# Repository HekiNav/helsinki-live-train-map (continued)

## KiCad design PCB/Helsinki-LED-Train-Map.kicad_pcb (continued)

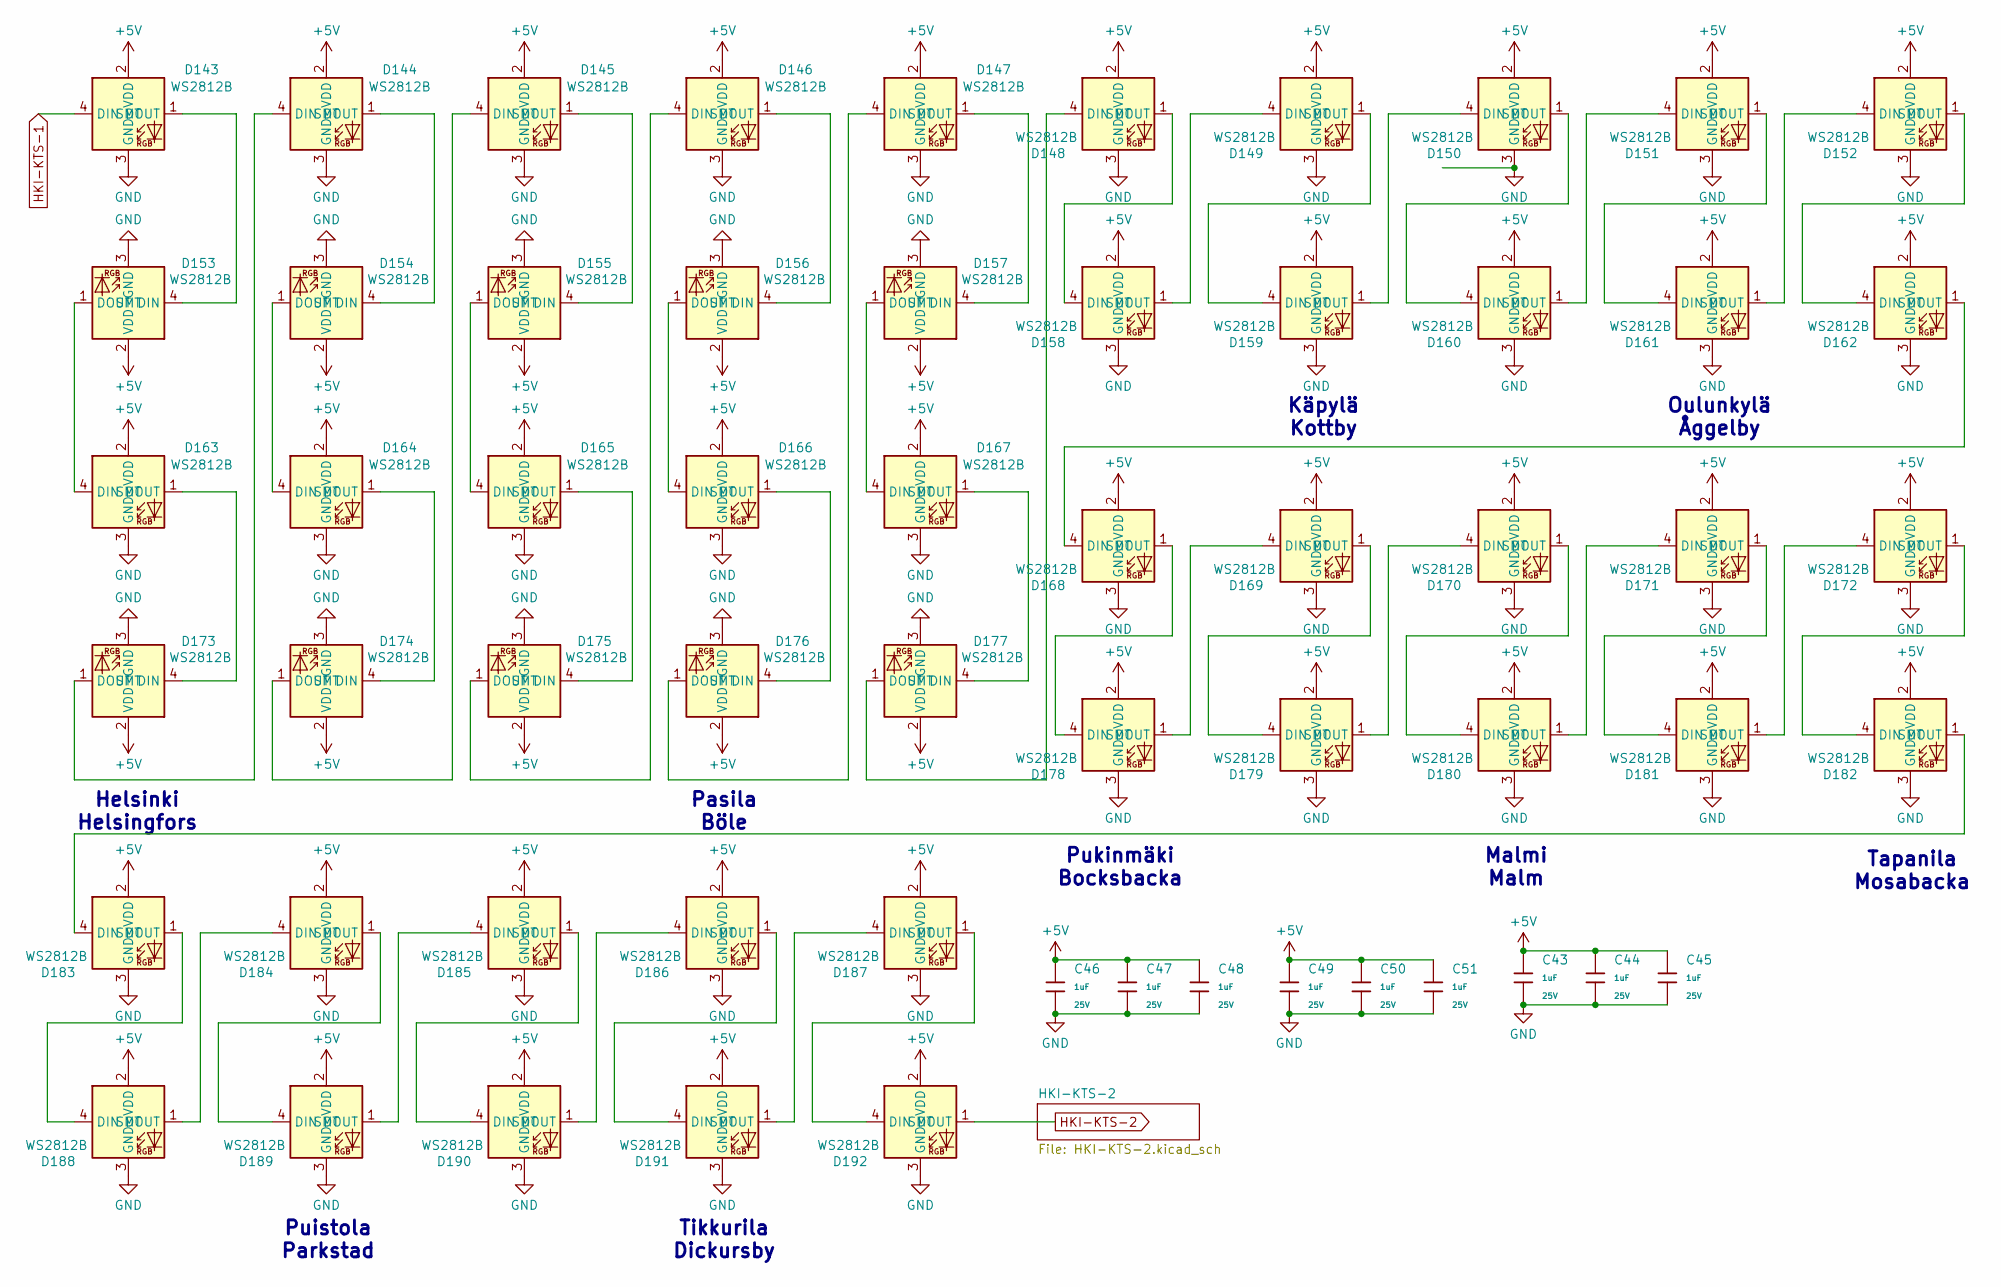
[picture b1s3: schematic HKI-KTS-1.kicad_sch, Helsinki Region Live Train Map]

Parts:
C43, C44, C45, C46, C47, C48, C49, C50, C51: 1uF; C_0402; Voltage Rated 25V; Tolerance ±10%; Part CL05A105KA5NQNC; LCSC C52923
D143, D144, D145, D146, D147, D148, D149, D150, D151, D152, D153, D154, D155, D156, D157, D158, D159, D160, D161, D162, D163, D164, D165, D166, D167, D168, D169, D170, D171, D172, D173, D174, D175, D176, D177, D178, D179, D180, D181, D182, D183, D184, D185, D186, D187, D188, D189, D190, D191, D192: WS2812B; LED-SMD_4P-L1.6-W1.5_XL-1615RGBC-WS2812B; Part XL-1615RGBC-WS2812B; LCSC C5349954

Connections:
+5V: C43.1, C44.1, C45.1, C46.1, C47.1, C48.1, C49.1, C50.1, C51.1, D143.2 (VDD), D144.2 (VDD), D145.2 (VDD), D146.2 (VDD), D147.2 (VDD), D148.2 (VDD), D149.2 (VDD), D150.2 (VDD), D151.2 (VDD), D152.2 (VDD), D153.2 (VDD), D154.2 (VDD), D155.2 (VDD), D156.2 (VDD), D157.2 (VDD), D158.2 (VDD), D159.2 (VDD), D160.2 (VDD), D161.2 (VDD), D162.2 (VDD), D163.2 (VDD), D164.2 (VDD), D165.2 (VDD), D166.2 (VDD), D167.2 (VDD), D168.2 (VDD), D169.2 (VDD), D170.2 (VDD), D171.2 (VDD), D172.2 (VDD), D173.2 (VDD), D174.2 (VDD), D175.2 (VDD), D176.2 (VDD), D177.2 (VDD), D178.2 (VDD), D179.2 (VDD), D180.2 (VDD), D181.2 (VDD), D182.2 (VDD), D183.2 (VDD), D184.2 (VDD), D185.2 (VDD), D186.2 (VDD), D187.2 (VDD), D188.2 (VDD), D189.2 (VDD), D190.2 (VDD), D191.2 (VDD), D192.2 (VDD); also elsewhere on the board
GND: C43.2, C44.2, C45.2, C46.2, C47.2, C48.2, C49.2, C50.2, C51.2, D143.3 (GND), D144.3 (GND), D145.3 (GND), D146.3 (GND), D147.3 (GND), D148.3 (GND), D149.3 (GND), D150.3 (GND), D151.3 (GND), D152.3 (GND), D153.3 (GND), D154.3 (GND), D155.3 (GND), D156.3 (GND), D157.3 (GND), D158.3 (GND), D159.3 (GND), D160.3 (GND), D161.3 (GND), D162.3 (GND), D163.3 (GND), D164.3 (GND), D165.3 (GND), D166.3 (GND), D167.3 (GND), D168.3 (GND), D169.3 (GND), D170.3 (GND), D171.3 (GND), D172.3 (GND), D173.3 (GND), D174.3 (GND), D175.3 (GND), D176.3 (GND), D177.3 (GND), D178.3 (GND), D179.3 (GND), D180.3 (GND), D181.3 (GND), D182.3 (GND), D183.3 (GND), D184.3 (GND), D185.3 (GND), D186.3 (GND), D187.3 (GND), D188.3 (GND), D189.3 (GND), D190.3 (GND), D191.3 (GND), D192.3 (GND); also elsewhere on the board
HKI-KTS-1: D143.4 (DIN); also elsewhere on the board
HKI-KTS-2: D192.1 (DOUT); also elsewhere on the board
unnamed: D143.1 (DOUT), D153.4 (DIN)
unnamed: D144.4 (DIN), D173.1 (DOUT)
unnamed: D144.1 (DOUT), D154.4 (DIN)
unnamed: D145.4 (DIN), D174.1 (DOUT)
unnamed: D145.1 (DOUT), D155.4 (DIN)
unnamed: D146.4 (DIN), D175.1 (DOUT)
unnamed: D146.1 (DOUT), D156.4 (DIN)
unnamed: D147.4 (DIN), D176.1 (DOUT)
unnamed: D147.1 (DOUT), D157.4 (DIN)
unnamed: D148.4 (DIN), D177.1 (DOUT)
unnamed: D148.1 (DOUT), D158.4 (DIN)
unnamed: D149.4 (DIN), D158.1 (DOUT)
unnamed: D149.1 (DOUT), D159.4 (DIN)
unnamed: D150.4 (DIN), D159.1 (DOUT)
unnamed: D150.1 (DOUT), D160.4 (DIN)
unnamed: D151.4 (DIN), D160.1 (DOUT)
unnamed: D151.1 (DOUT), D161.4 (DIN)
unnamed: D152.4 (DIN), D161.1 (DOUT)
unnamed: D152.1 (DOUT), D162.4 (DIN)
unnamed: D153.1 (DOUT), D163.4 (DIN)
unnamed: D154.1 (DOUT), D164.4 (DIN)
unnamed: D155.1 (DOUT), D165.4 (DIN)
unnamed: D156.1 (DOUT), D166.4 (DIN)
unnamed: D157.1 (DOUT), D167.4 (DIN)
unnamed: D162.1 (DOUT), D168.4 (DIN)
unnamed: D163.1 (DOUT), D173.4 (DIN)
unnamed: D164.1 (DOUT), D174.4 (DIN)
unnamed: D165.1 (DOUT), D175.4 (DIN)
unnamed: D166.1 (DOUT), D176.4 (DIN)
unnamed: D167.1 (DOUT), D177.4 (DIN)
unnamed: D168.1 (DOUT), D178.4 (DIN)
unnamed: D169.4 (DIN), D178.1 (DOUT)
unnamed: D169.1 (DOUT), D179.4 (DIN)
unnamed: D170.4 (DIN), D179.1 (DOUT)
unnamed: D170.1 (DOUT), D180.4 (DIN)
unnamed: D171.4 (DIN), D180.1 (DOUT)
unnamed: D171.1 (DOUT), D181.4 (DIN)
unnamed: D172.4 (DIN), D181.1 (DOUT)
unnamed: D172.1 (DOUT), D182.4 (DIN)
unnamed: D182.1 (DOUT), D183.4 (DIN)
unnamed: D183.1 (DOUT), D188.4 (DIN)
unnamed: D184.4 (DIN), D188.1 (DOUT)
unnamed: D184.1 (DOUT), D189.4 (DIN)
unnamed: D185.4 (DIN), D189.1 (DOUT)
unnamed: D185.1 (DOUT), D190.4 (DIN)
unnamed: D186.4 (DIN), D190.1 (DOUT)
unnamed: D186.1 (DOUT), D191.4 (DIN)
unnamed: D187.4 (DIN), D191.1 (DOUT)
unnamed: D187.1 (DOUT), D192.4 (DIN)

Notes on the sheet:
Puistola Parkstad
Malmi Malm
Tapanila Mosabacka
Pasila Böle
Oulunkylä Åggelby
Käpylä Kottby
Helsinki Helsingfors
Pukinmäki Bocksbacka
Tikkurila Dickursby

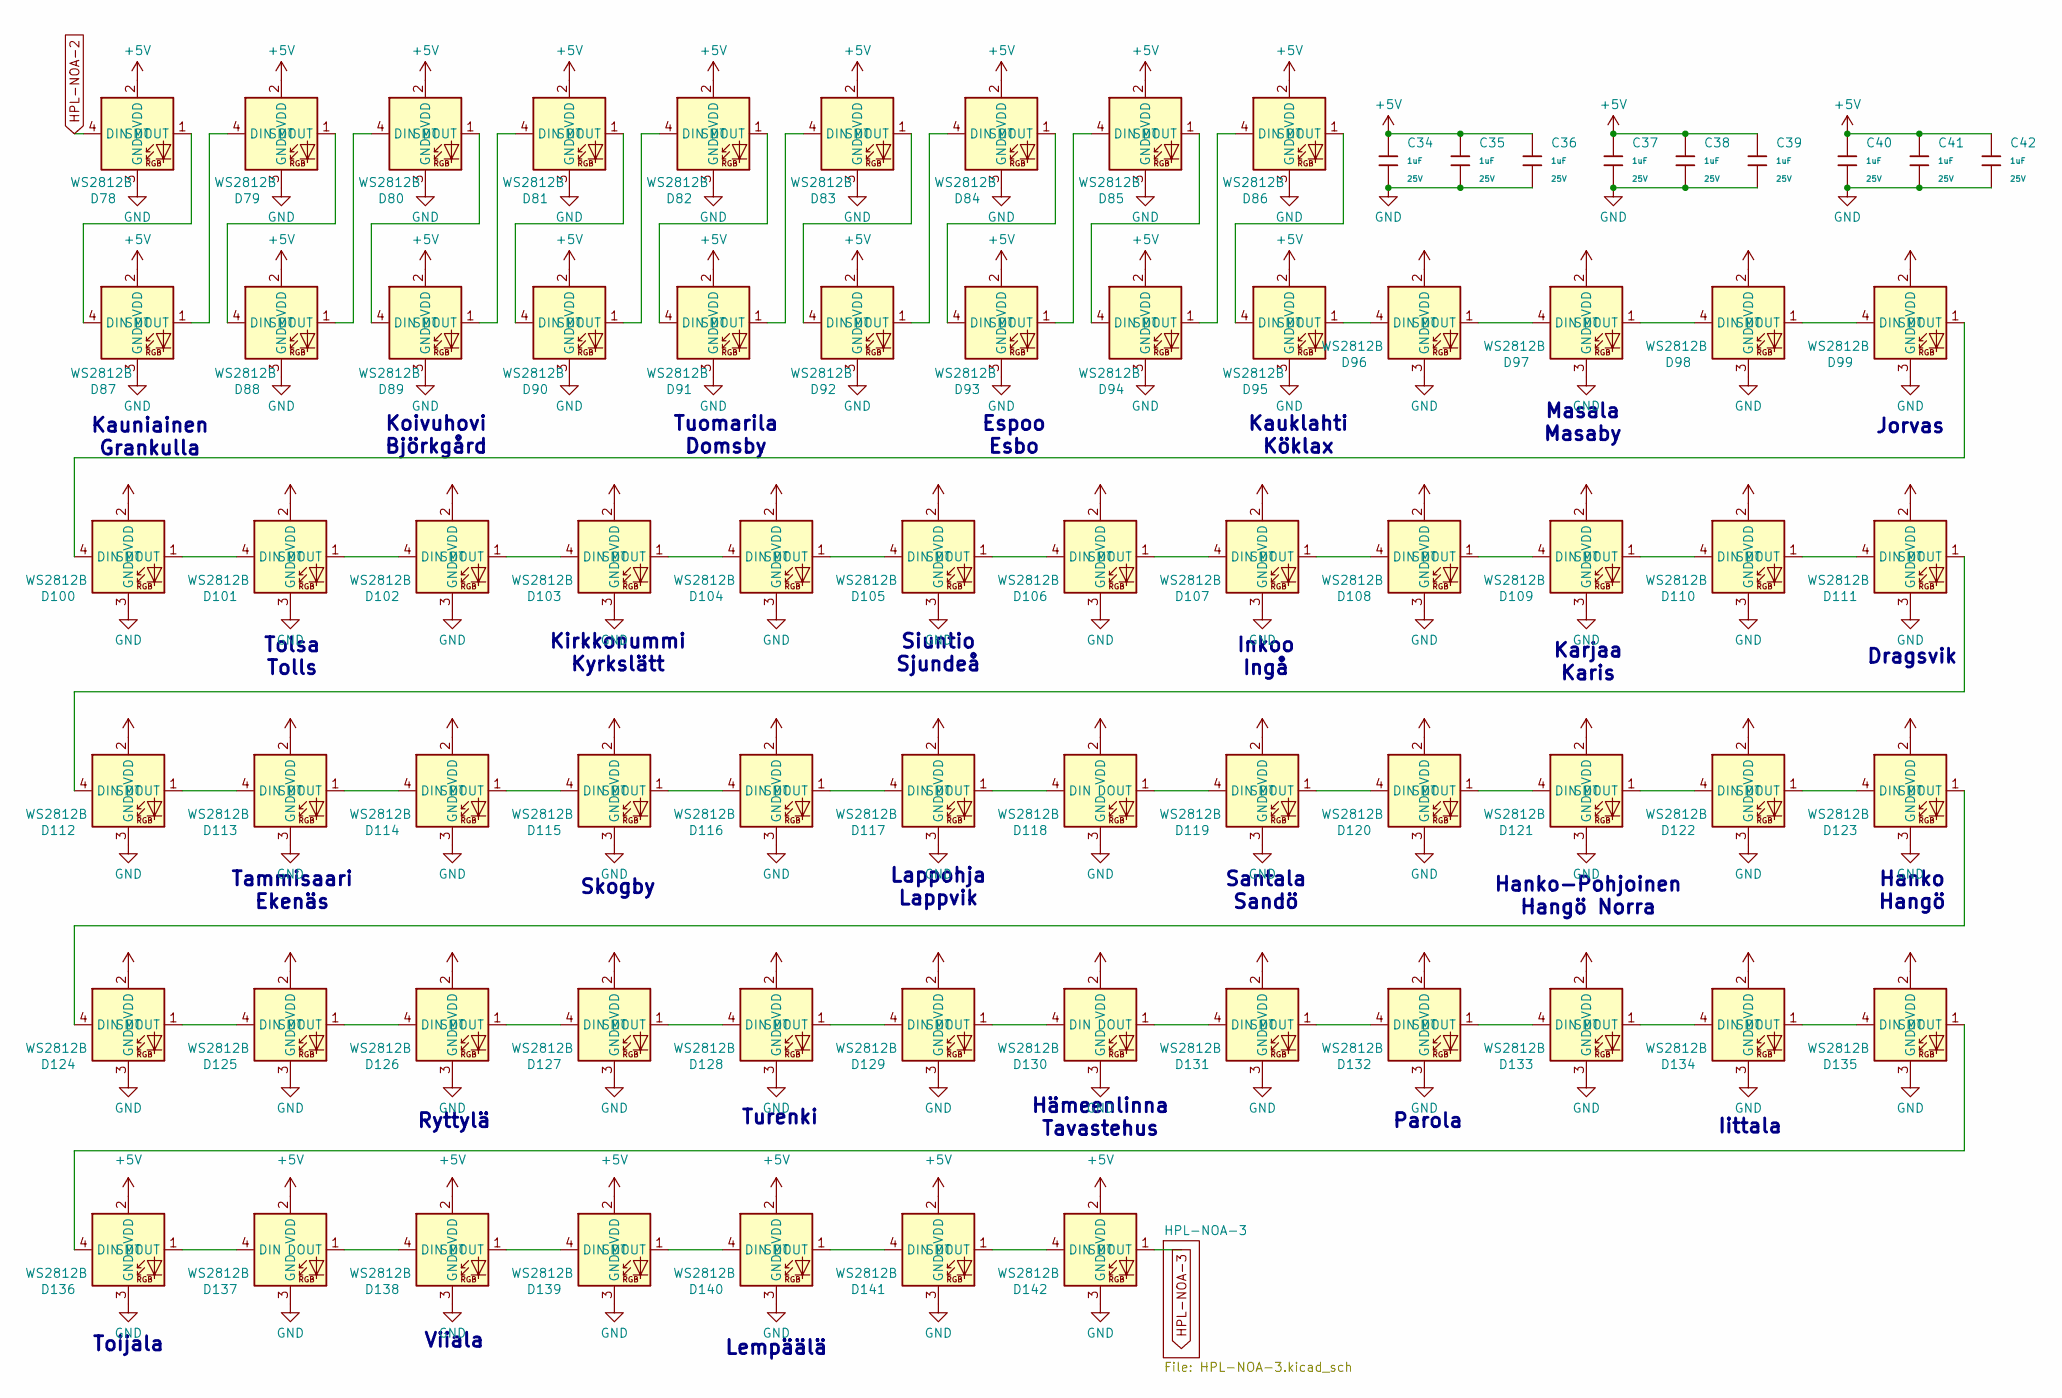
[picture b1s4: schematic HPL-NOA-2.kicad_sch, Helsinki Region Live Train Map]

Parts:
C34, C35, C36, C37, C38, C39, C40, C41, C42: 1uF; C_0402; Voltage Rated 25V; Tolerance ±10%; Part CL05A105KA5NQNC; LCSC C52923
D78, D79, D80, D81, D82, D83, D84, D85, D86, D87, D88, D89, D90, D91, D92, D93, D94, D95, D96, D97, D98, D99, D100, D101, D102, D103, D104, D105, D106, D107, D108, D109, D110, D111, D112, D113, D114, D115, D116, D117, D118, D119, D120, D121, D122, D123, D124, D125, D126, D127, D128, D129, D130, D131, D132, D133, D134, D135, D136, D137, D138, D139, D140, D141, D142: WS2812B; LED-SMD_4P-L1.6-W1.5_XL-1615RGBC-WS2812B; Part XL-1615RGBC-WS2812B; LCSC C5349954

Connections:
+5V: C34.1, C35.1, C36.1, C37.1, C38.1, C39.1, C40.1, C41.1, C42.1, D78.2 (VDD), D79.2 (VDD), D80.2 (VDD), D81.2 (VDD), D82.2 (VDD), D83.2 (VDD), D84.2 (VDD), D85.2 (VDD), D86.2 (VDD), D87.2 (VDD), D88.2 (VDD), D89.2 (VDD), D90.2 (VDD), D91.2 (VDD), D92.2 (VDD), D93.2 (VDD), D94.2 (VDD), D95.2 (VDD), D96.2 (VDD), D97.2 (VDD), D98.2 (VDD), D99.2 (VDD), D100.2 (VDD), D101.2 (VDD), D102.2 (VDD), D103.2 (VDD), D104.2 (VDD), D105.2 (VDD), D106.2 (VDD), D107.2 (VDD), D108.2 (VDD), D109.2 (VDD), D110.2 (VDD), D111.2 (VDD), D112.2 (VDD), D113.2 (VDD), D114.2 (VDD), D115.2 (VDD), D116.2 (VDD), D117.2 (VDD), D118.2 (VDD), D119.2 (VDD), D120.2 (VDD), D121.2 (VDD), D122.2 (VDD), D123.2 (VDD), D124.2 (VDD), D125.2 (VDD), D126.2 (VDD), D127.2 (VDD), D128.2 (VDD), D129.2 (VDD), D130.2 (VDD), D131.2 (VDD), D132.2 (VDD), D133.2 (VDD), D134.2 (VDD), D135.2 (VDD), D136.2 (VDD), D137.2 (VDD), D138.2 (VDD), D139.2 (VDD), D140.2 (VDD), D141.2 (VDD), D142.2 (VDD); also elsewhere on the board
GND: C34.2, C35.2, C36.2, C37.2, C38.2, C39.2, C40.2, C41.2, C42.2, D78.3 (GND), D79.3 (GND), D80.3 (GND), D81.3 (GND), D82.3 (GND), D83.3 (GND), D84.3 (GND), D85.3 (GND), D86.3 (GND), D87.3 (GND), D88.3 (GND), D89.3 (GND), D90.3 (GND), D91.3 (GND), D92.3 (GND), D93.3 (GND), D94.3 (GND), D95.3 (GND), D96.3 (GND), D97.3 (GND), D98.3 (GND), D99.3 (GND), D100.3 (GND), D101.3 (GND), D102.3 (GND), D103.3 (GND), D104.3 (GND), D105.3 (GND), D106.3 (GND), D107.3 (GND), D108.3 (GND), D109.3 (GND), D110.3 (GND), D111.3 (GND), D112.3 (GND), D113.3 (GND), D114.3 (GND), D115.3 (GND), D116.3 (GND), D117.3 (GND), D118.3 (GND), D119.3 (GND), D120.3 (GND), D121.3 (GND), D122.3 (GND), D123.3 (GND), D124.3 (GND), D125.3 (GND), D126.3 (GND), D127.3 (GND), D128.3 (GND), D129.3 (GND), D130.3 (GND), D131.3 (GND), D132.3 (GND), D133.3 (GND), D134.3 (GND), D135.3 (GND), D136.3 (GND), D137.3 (GND), D138.3 (GND), D139.3 (GND), D140.3 (GND), D141.3 (GND), D142.3 (GND); also elsewhere on the board
HPL-NOA-2: D78.4 (DIN); also elsewhere on the board
HPL-NOA-3: D142.1 (DOUT); also elsewhere on the board
unnamed: D78.1 (DOUT), D87.4 (DIN)
unnamed: D79.4 (DIN), D87.1 (DOUT)
unnamed: D79.1 (DOUT), D88.4 (DIN)
unnamed: D80.4 (DIN), D88.1 (DOUT)
unnamed: D80.1 (DOUT), D89.4 (DIN)
unnamed: D81.4 (DIN), D89.1 (DOUT)
unnamed: D81.1 (DOUT), D90.4 (DIN)
unnamed: D82.4 (DIN), D90.1 (DOUT)
unnamed: D82.1 (DOUT), D91.4 (DIN)
unnamed: D83.4 (DIN), D91.1 (DOUT)
unnamed: D83.1 (DOUT), D92.4 (DIN)
unnamed: D84.4 (DIN), D92.1 (DOUT)
unnamed: D84.1 (DOUT), D93.4 (DIN)
unnamed: D85.4 (DIN), D93.1 (DOUT)
unnamed: D85.1 (DOUT), D94.4 (DIN)
unnamed: D86.4 (DIN), D94.1 (DOUT)
unnamed: D86.1 (DOUT), D95.4 (DIN)
unnamed: D95.1 (DOUT), D96.4 (DIN)
unnamed: D96.1 (DOUT), D97.4 (DIN)
unnamed: D97.1 (DOUT), D98.4 (DIN)
unnamed: D98.1 (DOUT), D99.4 (DIN)
unnamed: D99.1 (DOUT), D100.4 (DIN)
unnamed: D100.1 (DOUT), D101.4 (DIN)
unnamed: D101.1 (DOUT), D102.4 (DIN)
unnamed: D102.1 (DOUT), D103.4 (DIN)
unnamed: D103.1 (DOUT), D104.4 (DIN)
unnamed: D104.1 (DOUT), D105.4 (DIN)
unnamed: D105.1 (DOUT), D106.4 (DIN)
unnamed: D106.1 (DOUT), D107.4 (DIN)
unnamed: D107.1 (DOUT), D108.4 (DIN)
unnamed: D108.1 (DOUT), D109.4 (DIN)
unnamed: D109.1 (DOUT), D110.4 (DIN)
unnamed: D110.1 (DOUT), D111.4 (DIN)
unnamed: D111.1 (DOUT), D112.4 (DIN)
unnamed: D112.1 (DOUT), D113.4 (DIN)
unnamed: D113.1 (DOUT), D114.4 (DIN)
unnamed: D114.1 (DOUT), D115.4 (DIN)
unnamed: D115.1 (DOUT), D116.4 (DIN)
unnamed: D116.1 (DOUT), D117.4 (DIN)
unnamed: D117.1 (DOUT), D118.4 (DIN)
unnamed: D118.1 (DOUT), D119.4 (DIN)
unnamed: D119.1 (DOUT), D120.4 (DIN)
unnamed: D120.1 (DOUT), D121.4 (DIN)
unnamed: D121.1 (DOUT), D122.4 (DIN)
unnamed: D122.1 (DOUT), D123.4 (DIN)
unnamed: D123.1 (DOUT), D124.4 (DIN)
unnamed: D124.1 (DOUT), D125.4 (DIN)
unnamed: D125.1 (DOUT), D126.4 (DIN)
unnamed: D126.1 (DOUT), D127.4 (DIN)
unnamed: D127.1 (DOUT), D128.4 (DIN)
unnamed: D128.1 (DOUT), D129.4 (DIN)
unnamed: D129.1 (DOUT), D130.4 (DIN)
unnamed: D130.1 (DOUT), D131.4 (DIN)
unnamed: D131.1 (DOUT), D132.4 (DIN)
unnamed: D132.1 (DOUT), D133.4 (DIN)
unnamed: D133.1 (DOUT), D134.4 (DIN)
unnamed: D134.1 (DOUT), D135.4 (DIN)
unnamed: D135.1 (DOUT), D136.4 (DIN)
unnamed: D136.1 (DOUT), D137.4 (DIN)
unnamed: D137.1 (DOUT), D138.4 (DIN)
unnamed: D138.1 (DOUT), D139.4 (DIN)
unnamed: D139.1 (DOUT), D140.4 (DIN)
unnamed: D140.1 (DOUT), D141.4 (DIN)
unnamed: D141.1 (DOUT), D142.4 (DIN)

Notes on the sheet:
Turenki
Inkoo Ingå
Tolsa Tolls
Hanko Hangö
Koivuhovi Björkgård
Lappohja Lappvik
Espoo Esbo
Lempäälä
Viiala
Skogby
Dragsvik
Tammisaari Ekenäs
Hämeenlinna Tavastehus
Santala Sandö
Masala Masaby
Hanko-Pohjoinen Hangö Norra
Toijala
Jorvas
Siuntio Sjundeå
Kauklahti Köklax
Tuomarila Domsby
Kauniainen Grankulla
Ryttylä
Kirkkonummi Kyrkslätt
Iittala
Parola
Karjaa Karis

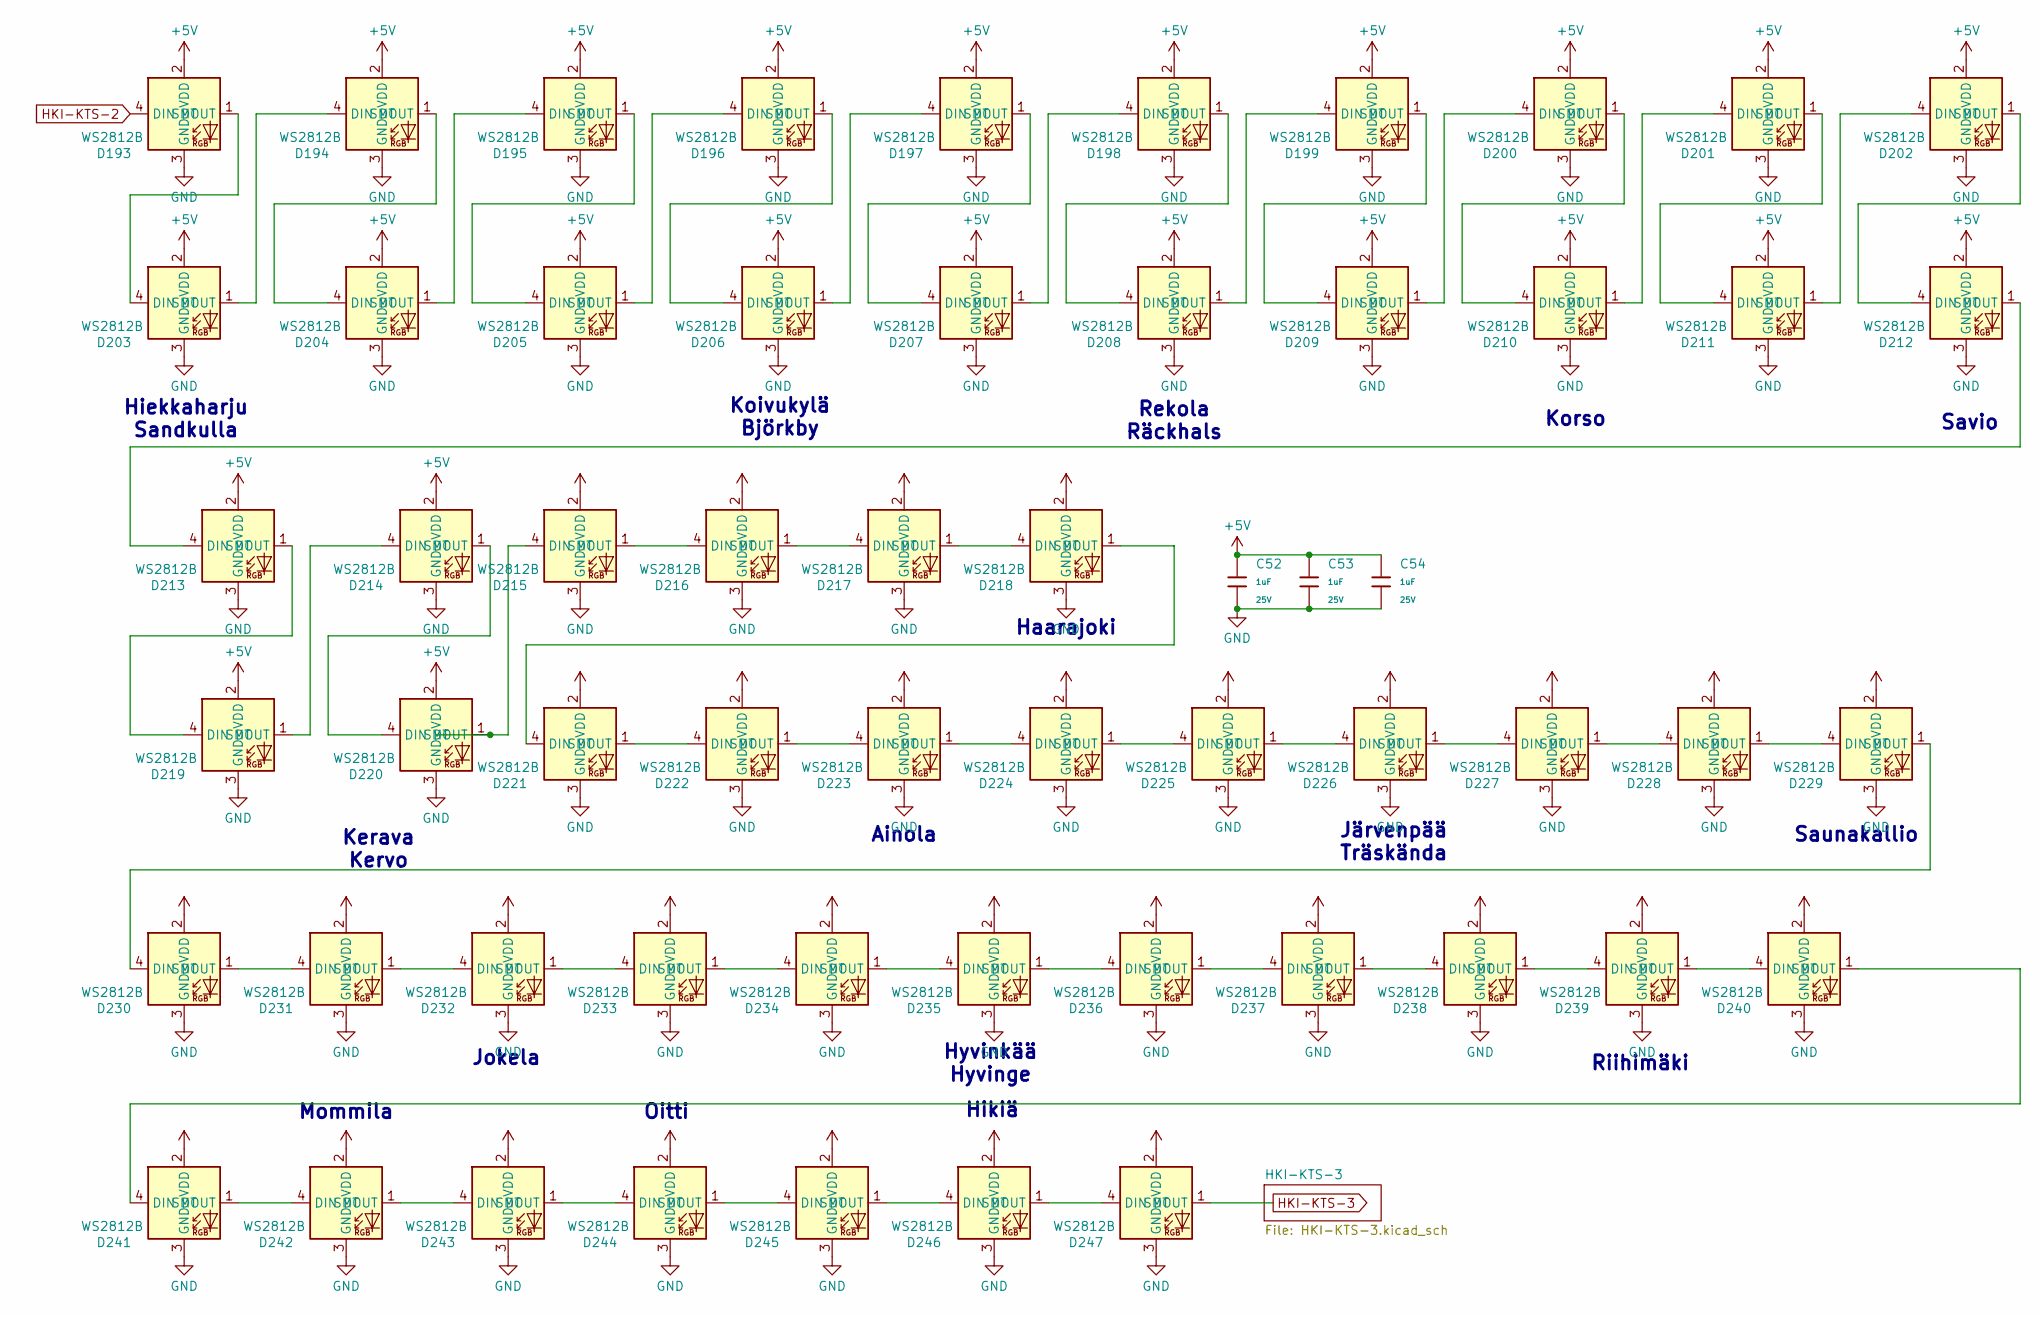
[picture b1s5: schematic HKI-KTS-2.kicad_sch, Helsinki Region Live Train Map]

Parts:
C52, C53, C54: 1uF; C_0402; Voltage Rated 25V; Tolerance ±10%; Part CL05A105KA5NQNC; LCSC C52923
D193, D194, D195, D196, D197, D198, D199, D200, D201, D202, D203, D204, D205, D206, D207, D208, D209, D210, D211, D212, D213, D214, D215, D216, D217, D218, D219, D220, D221, D222, D223, D224, D225, D226, D227, D228, D229, D230, D231, D232, D233, D234, D235, D236, D237, D238, D239, D240, D241, D242, D243, D244, D245, D246, D247: WS2812B; LED-SMD_4P-L1.6-W1.5_XL-1615RGBC-WS2812B; Part XL-1615RGBC-WS2812B; LCSC C5349954

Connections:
+5V: C52.1, C53.1, C54.1, D193.2 (VDD), D194.2 (VDD), D195.2 (VDD), D196.2 (VDD), D197.2 (VDD), D198.2 (VDD), D199.2 (VDD), D200.2 (VDD), D201.2 (VDD), D202.2 (VDD), D203.2 (VDD), D204.2 (VDD), D205.2 (VDD), D206.2 (VDD), D207.2 (VDD), D208.2 (VDD), D209.2 (VDD), D210.2 (VDD), D211.2 (VDD), D212.2 (VDD), D213.2 (VDD), D214.2 (VDD), D215.2 (VDD), D216.2 (VDD), D217.2 (VDD), D218.2 (VDD), D219.2 (VDD), D220.2 (VDD), D221.2 (VDD), D222.2 (VDD), D223.2 (VDD), D224.2 (VDD), D225.2 (VDD), D226.2 (VDD), D227.2 (VDD), D228.2 (VDD), D229.2 (VDD), D230.2 (VDD), D231.2 (VDD), D232.2 (VDD), D233.2 (VDD), D234.2 (VDD), D235.2 (VDD), D236.2 (VDD), D237.2 (VDD), D238.2 (VDD), D239.2 (VDD), D240.2 (VDD), D241.2 (VDD), D242.2 (VDD), D243.2 (VDD), D244.2 (VDD), D245.2 (VDD), D246.2 (VDD), D247.2 (VDD); also elsewhere on the board
GND: C52.2, C53.2, C54.2, D193.3 (GND), D194.3 (GND), D195.3 (GND), D196.3 (GND), D197.3 (GND), D198.3 (GND), D199.3 (GND), D200.3 (GND), D201.3 (GND), D202.3 (GND), D203.3 (GND), D204.3 (GND), D205.3 (GND), D206.3 (GND), D207.3 (GND), D208.3 (GND), D209.3 (GND), D210.3 (GND), D211.3 (GND), D212.3 (GND), D213.3 (GND), D214.3 (GND), D215.3 (GND), D216.3 (GND), D217.3 (GND), D218.3 (GND), D219.3 (GND), D220.3 (GND), D221.3 (GND), D222.3 (GND), D223.3 (GND), D224.3 (GND), D225.3 (GND), D226.3 (GND), D227.3 (GND), D228.3 (GND), D229.3 (GND), D230.3 (GND), D231.3 (GND), D232.3 (GND), D233.3 (GND), D234.3 (GND), D235.3 (GND), D236.3 (GND), D237.3 (GND), D238.3 (GND), D239.3 (GND), D240.3 (GND), D241.3 (GND), D242.3 (GND), D243.3 (GND), D244.3 (GND), D245.3 (GND), D246.3 (GND), D247.3 (GND); also elsewhere on the board
HKI-KTS-2: D193.4 (DIN); also elsewhere on the board
HKI-KTS-3: D247.1 (DOUT); also elsewhere on the board
unnamed: D193.1 (DOUT), D203.4 (DIN)
unnamed: D194.4 (DIN), D203.1 (DOUT)
unnamed: D194.1 (DOUT), D204.4 (DIN)
unnamed: D195.4 (DIN), D204.1 (DOUT)
unnamed: D195.1 (DOUT), D205.4 (DIN)
unnamed: D196.4 (DIN), D205.1 (DOUT)
unnamed: D196.1 (DOUT), D206.4 (DIN)
unnamed: D197.4 (DIN), D206.1 (DOUT)
unnamed: D197.1 (DOUT), D207.4 (DIN)
unnamed: D198.4 (DIN), D207.1 (DOUT)
unnamed: D198.1 (DOUT), D208.4 (DIN)
unnamed: D199.4 (DIN), D208.1 (DOUT)
unnamed: D199.1 (DOUT), D209.4 (DIN)
unnamed: D200.4 (DIN), D209.1 (DOUT)
unnamed: D200.1 (DOUT), D210.4 (DIN)
unnamed: D201.4 (DIN), D210.1 (DOUT)
unnamed: D201.1 (DOUT), D211.4 (DIN)
unnamed: D202.4 (DIN), D211.1 (DOUT)
unnamed: D202.1 (DOUT), D212.4 (DIN)
unnamed: D212.1 (DOUT), D213.4 (DIN)
unnamed: D213.1 (DOUT), D219.4 (DIN)
unnamed: D214.4 (DIN), D219.1 (DOUT)
unnamed: D214.1 (DOUT), D220.4 (DIN)
unnamed: D215.4 (DIN), D220.1 (DOUT)
unnamed: D215.1 (DOUT), D216.4 (DIN)
unnamed: D216.1 (DOUT), D217.4 (DIN)
unnamed: D217.1 (DOUT), D218.4 (DIN)
unnamed: D218.1 (DOUT), D221.4 (DIN)
unnamed: D221.1 (DOUT), D222.4 (DIN)
unnamed: D222.1 (DOUT), D223.4 (DIN)
unnamed: D223.1 (DOUT), D224.4 (DIN)
unnamed: D224.1 (DOUT), D225.4 (DIN)
unnamed: D225.1 (DOUT), D226.4 (DIN)
unnamed: D226.1 (DOUT), D227.4 (DIN)
unnamed: D227.1 (DOUT), D228.4 (DIN)
unnamed: D228.1 (DOUT), D229.4 (DIN)
unnamed: D229.1 (DOUT), D230.4 (DIN)
unnamed: D230.1 (DOUT), D231.4 (DIN)
unnamed: D231.1 (DOUT), D232.4 (DIN)
unnamed: D232.1 (DOUT), D233.4 (DIN)
unnamed: D233.1 (DOUT), D234.4 (DIN)
unnamed: D234.1 (DOUT), D235.4 (DIN)
unnamed: D235.1 (DOUT), D236.4 (DIN)
unnamed: D236.1 (DOUT), D237.4 (DIN)
unnamed: D237.1 (DOUT), D238.4 (DIN)
unnamed: D238.1 (DOUT), D239.4 (DIN)
unnamed: D239.1 (DOUT), D240.4 (DIN)
unnamed: D240.1 (DOUT), D241.4 (DIN)
unnamed: D241.1 (DOUT), D242.4 (DIN)
unnamed: D242.1 (DOUT), D243.4 (DIN)
unnamed: D243.1 (DOUT), D244.4 (DIN)
unnamed: D244.1 (DOUT), D245.4 (DIN)
unnamed: D245.1 (DOUT), D246.4 (DIN)
unnamed: D246.1 (DOUT), D247.4 (DIN)

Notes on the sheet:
Rekola Räckhals
Oitti
Kerava Kervo
Savio
Järvenpää Träskända
Riihimäki
Ainola
Jokela
Haarajoki
Saunakallio
Hiekkaharju Sandkulla
Mommila
Koivukylä Björkby
Korso
Hyvinkää Hyvinge
Hikiä

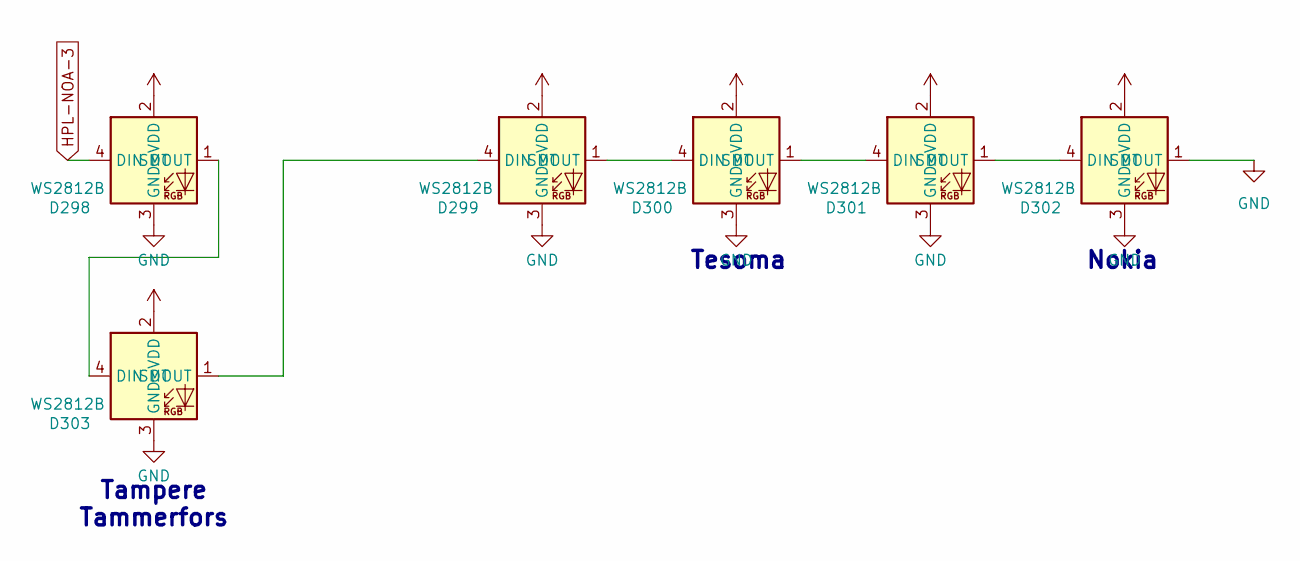
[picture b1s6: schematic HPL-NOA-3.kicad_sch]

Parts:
D298, D299, D300, D301, D302, D303: WS2812B; LED-SMD_4P-L1.6-W1.5_XL-1615RGBC-WS2812B; Part XL-1615RGBC-WS2812B; LCSC C5349954

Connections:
+5V: D298.2 (VDD), D299.2 (VDD), D300.2 (VDD), D301.2 (VDD), D302.2 (VDD), D303.2 (VDD); also elsewhere on the board
GND: D298.3 (GND), D299.3 (GND), D300.3 (GND), D301.3 (GND), D302.1 (DOUT), D302.3 (GND), D303.3 (GND); also elsewhere on the board
HPL-NOA-3: D298.4 (DIN); also elsewhere on the board
unnamed: D298.1 (DOUT), D303.4 (DIN)
unnamed: D299.4 (DIN), D303.1 (DOUT)
unnamed: D299.1 (DOUT), D300.4 (DIN)
unnamed: D300.1 (DOUT), D301.4 (DIN)
unnamed: D301.1 (DOUT), D302.4 (DIN)

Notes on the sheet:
Tesoma
Nokia
Tampere Tammerfors

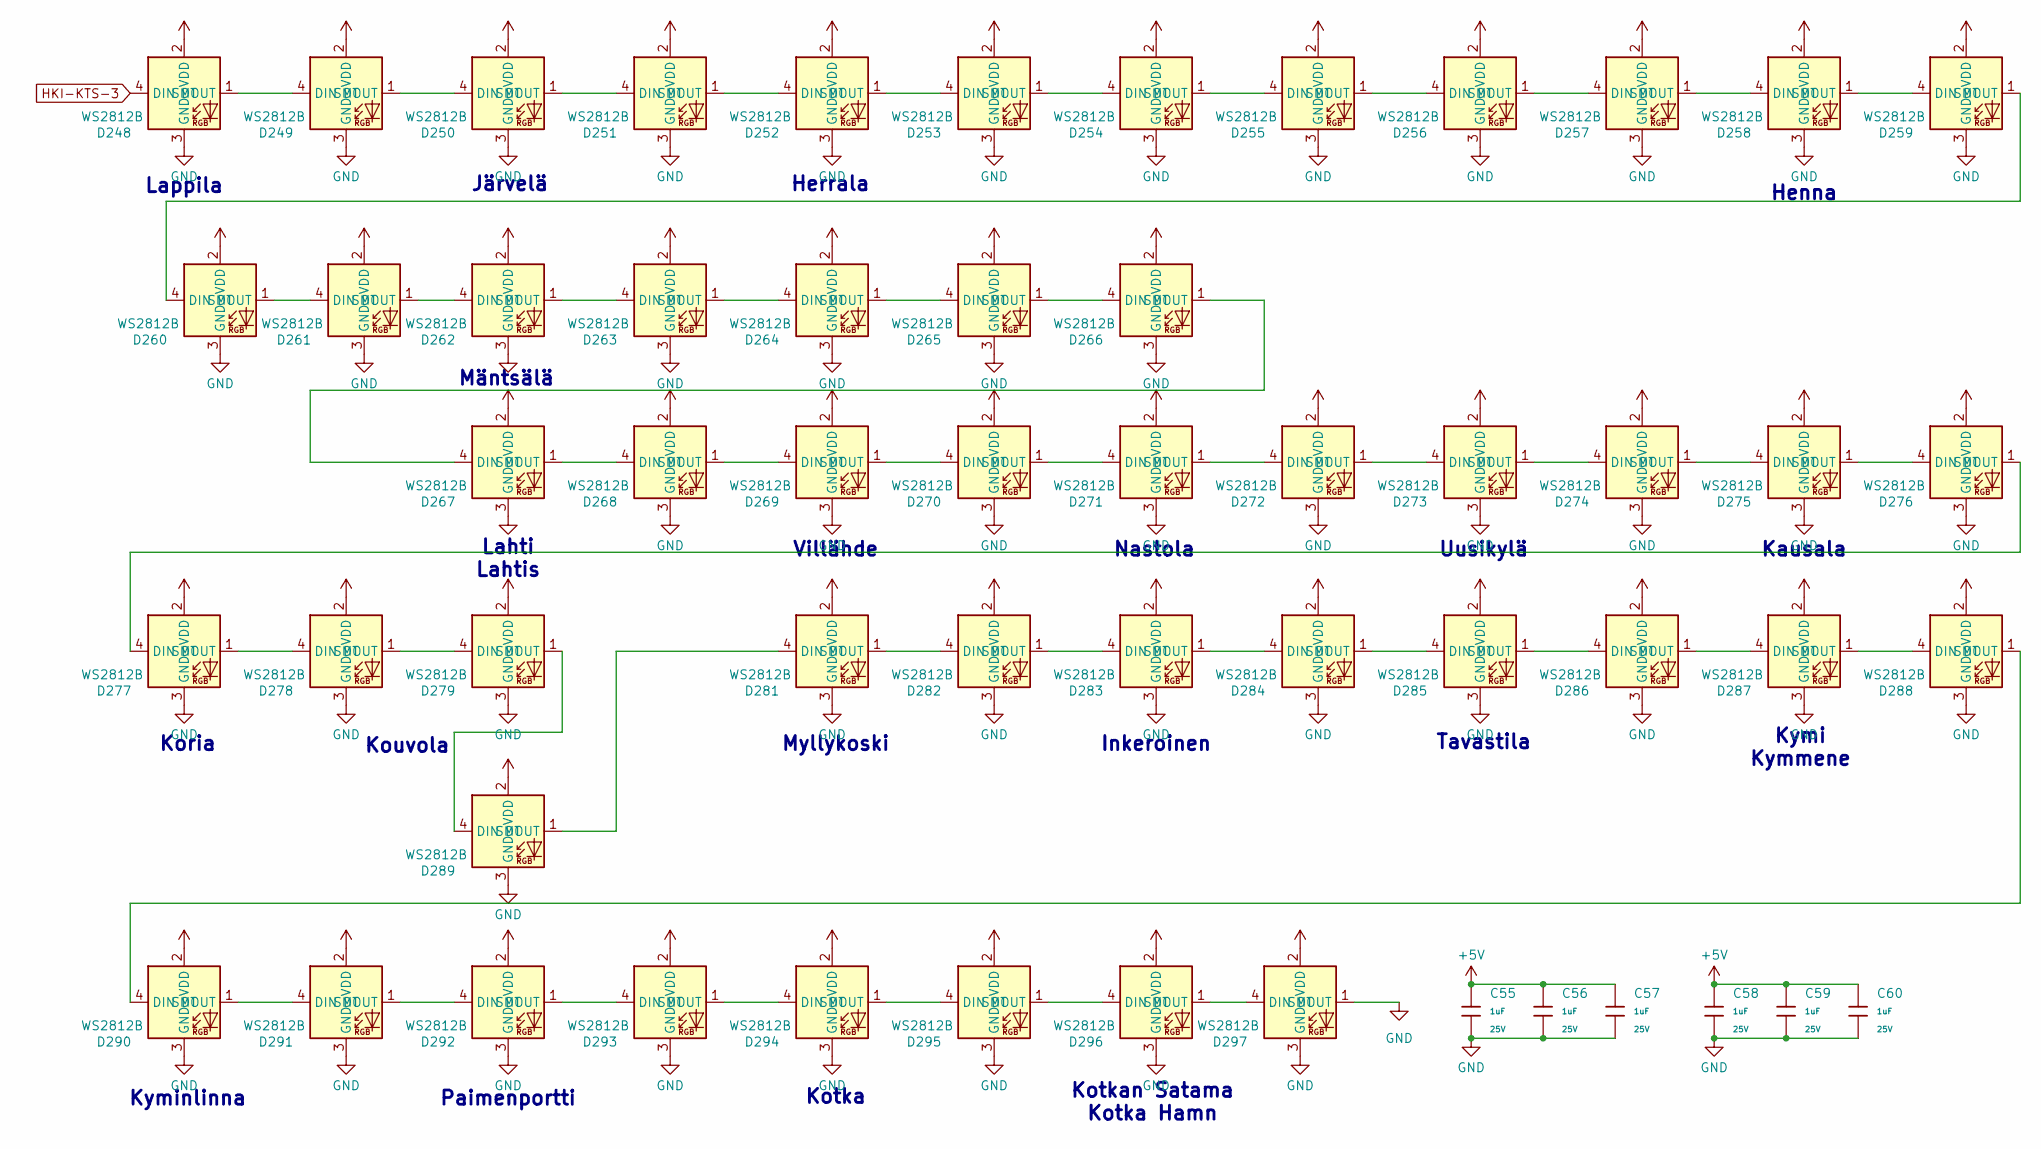
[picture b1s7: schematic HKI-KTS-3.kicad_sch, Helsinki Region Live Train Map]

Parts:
C55, C56, C57, C58, C59, C60: 1uF; C_0402; Voltage Rated 25V; Tolerance ±10%; Part CL05A105KA5NQNC; LCSC C52923
D248, D249, D250, D251, D252, D253, D254, D255, D256, D257, D258, D259, D260, D261, D262, D263, D264, D265, D266, D267, D268, D269, D270, D271, D272, D273, D274, D275, D276, D277, D278, D279, D281, D282, D283, D284, D285, D286, D287, D288, D289, D290, D291, D292, D293, D294, D295, D296, D297: WS2812B; LED-SMD_4P-L1.6-W1.5_XL-1615RGBC-WS2812B; Part XL-1615RGBC-WS2812B; LCSC C5349954

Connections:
+5V: C55.1, C56.1, C57.1, C58.1, C59.1, C60.1, D248.2 (VDD), D249.2 (VDD), D250.2 (VDD), D251.2 (VDD), D252.2 (VDD), D253.2 (VDD), D254.2 (VDD), D255.2 (VDD), D256.2 (VDD), D257.2 (VDD), D258.2 (VDD), D259.2 (VDD), D260.2 (VDD), D261.2 (VDD), D262.2 (VDD), D263.2 (VDD), D264.2 (VDD), D265.2 (VDD), D266.2 (VDD), D267.2 (VDD), D268.2 (VDD), D269.2 (VDD), D270.2 (VDD), D271.2 (VDD), D272.2 (VDD), D273.2 (VDD), D274.2 (VDD), D275.2 (VDD), D276.2 (VDD), D277.2 (VDD), D278.2 (VDD), D279.2 (VDD), D281.2 (VDD), D282.2 (VDD), D283.2 (VDD), D284.2 (VDD), D285.2 (VDD), D286.2 (VDD), D287.2 (VDD), D288.2 (VDD), D289.2 (VDD), D290.2 (VDD), D291.2 (VDD), D292.2 (VDD), D293.2 (VDD), D294.2 (VDD), D295.2 (VDD), D296.2 (VDD), D297.2 (VDD); also elsewhere on the board
GND: C55.2, C56.2, C57.2, C58.2, C59.2, C60.2, D248.3 (GND), D249.3 (GND), D250.3 (GND), D251.3 (GND), D252.3 (GND), D253.3 (GND), D254.3 (GND), D255.3 (GND), D256.3 (GND), D257.3 (GND), D258.3 (GND), D259.3 (GND), D260.3 (GND), D261.3 (GND), D262.3 (GND), D263.3 (GND), D264.3 (GND), D265.3 (GND), D266.3 (GND), D267.3 (GND), D268.3 (GND), D269.3 (GND), D270.3 (GND), D271.3 (GND), D272.3 (GND), D273.3 (GND), D274.3 (GND), D275.3 (GND), D276.3 (GND), D277.3 (GND), D278.3 (GND), D279.3 (GND), D281.3 (GND), D282.3 (GND), D283.3 (GND), D284.3 (GND), D285.3 (GND), D286.3 (GND), D287.3 (GND), D288.3 (GND), D289.3 (GND), D290.3 (GND), D291.3 (GND), D292.3 (GND), D293.3 (GND), D294.3 (GND), D295.3 (GND), D296.3 (GND), D297.1 (DOUT), D297.3 (GND); also elsewhere on the board
HKI-KTS-3: D248.4 (DIN); also elsewhere on the board
unnamed: D248.1 (DOUT), D249.4 (DIN)
unnamed: D249.1 (DOUT), D250.4 (DIN)
unnamed: D250.1 (DOUT), D251.4 (DIN)
unnamed: D251.1 (DOUT), D252.4 (DIN)
unnamed: D252.1 (DOUT), D253.4 (DIN)
unnamed: D253.1 (DOUT), D254.4 (DIN)
unnamed: D254.1 (DOUT), D255.4 (DIN)
unnamed: D255.1 (DOUT), D256.4 (DIN)
unnamed: D256.1 (DOUT), D257.4 (DIN)
unnamed: D257.1 (DOUT), D258.4 (DIN)
unnamed: D258.1 (DOUT), D259.4 (DIN)
unnamed: D259.1 (DOUT), D260.4 (DIN)
unnamed: D260.1 (DOUT), D261.4 (DIN)
unnamed: D261.1 (DOUT), D262.4 (DIN)
unnamed: D262.1 (DOUT), D263.4 (DIN)
unnamed: D263.1 (DOUT), D264.4 (DIN)
unnamed: D264.1 (DOUT), D265.4 (DIN)
unnamed: D265.1 (DOUT), D266.4 (DIN)
unnamed: D266.1 (DOUT), D267.4 (DIN)
unnamed: D267.1 (DOUT), D268.4 (DIN)
unnamed: D268.1 (DOUT), D269.4 (DIN)
unnamed: D269.1 (DOUT), D270.4 (DIN)
unnamed: D270.1 (DOUT), D271.4 (DIN)
unnamed: D271.1 (DOUT), D272.4 (DIN)
unnamed: D272.1 (DOUT), D273.4 (DIN)
unnamed: D273.1 (DOUT), D274.4 (DIN)
unnamed: D274.1 (DOUT), D275.4 (DIN)
unnamed: D275.1 (DOUT), D276.4 (DIN)
unnamed: D276.1 (DOUT), D277.4 (DIN)
unnamed: D277.1 (DOUT), D278.4 (DIN)
unnamed: D278.1 (DOUT), D279.4 (DIN)
unnamed: D279.1 (DOUT), D289.4 (DIN)
unnamed: D281.4 (DIN), D289.1 (DOUT)
unnamed: D281.1 (DOUT), D282.4 (DIN)
unnamed: D282.1 (DOUT), D283.4 (DIN)
unnamed: D283.1 (DOUT), D284.4 (DIN)
unnamed: D284.1 (DOUT), D285.4 (DIN)
unnamed: D285.1 (DOUT), D286.4 (DIN)
unnamed: D286.1 (DOUT), D287.4 (DIN)
unnamed: D287.1 (DOUT), D288.4 (DIN)
unnamed: D288.1 (DOUT), D290.4 (DIN)
unnamed: D290.1 (DOUT), D291.4 (DIN)
unnamed: D291.1 (DOUT), D292.4 (DIN)
unnamed: D292.1 (DOUT), D293.4 (DIN)
unnamed: D293.1 (DOUT), D294.4 (DIN)
unnamed: D294.1 (DOUT), D295.4 (DIN)
unnamed: D295.1 (DOUT), D296.4 (DIN)
unnamed: D296.1 (DOUT), D297.4 (DIN)

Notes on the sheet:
Villähde
Kausala
Kotkan Satama Kotka Hamn
Lahti Lahtis
Inkeroinen
Uusikylä
Myllykoski
Nastola
Paimenportti
Henna
Tavastila
Kotka
Koria
Järvelä
Kymi Kymmene
Kouvola
Herrala
Kyminlinna
Mäntsälä
Lappila
